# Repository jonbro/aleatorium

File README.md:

# Aleatorium

A lua scriptable buddha box board swap.

The hardware on this project is forked from [Eric Brombaugh's RP2040 boardswap for buddha boxes](https://github.com/emeb/RP2040_Projects/tree/main/buddhabox). I'm so glad he opensourced this, a programmable buddha machine is something that I've long wanted.

The firmware contains an lua scriptable 8 channel synthesizer and sequencer. The synth has the following features:
- oscilators from MI braids  
- 1 assignable lfo + 2 semi assignable Envs per voice
- lowpass filter per voice
- reverb & delay send per voice

The sequencer is a callback that is run at 96ppq. All further sequencing must be done by you.

You write new songs for aleatorium by connecting to it with usb, and loading lua scripts onto it with the [web based code editor](https://github.com/jonbro/aleatorium-editor).

## Scripting API

The scripting interface is quite simple, but there are some example files, [jam1](Firmware/jam1.lua) and [jam2](Firmware/jam2.lua). The [globals.lua file](Firmware/globals.lua) contains parameter constants for altering the synth voices.

```
-- setParam(voiceNumber, targetParameter, value)
-- voiceNumber: 0-7, the voice you want to set
-- targetParameter: use the params table from globals.lua
-- value: 0-255. Some parameters take a value from globals here, see below
setParam(0, param.timbre, 80)

-- playNote(voiceNumber, midiNoteValue)
-- voiceNumber: 0-7, the voice you want to set
-- midiNoteValue: 60 is middle c
playNote(0, 60)

-- tempoSync
-- called 96 times per quarternote. Currently there is no way to set the bpm other than recompling the firmware.

function tempoSync()

end

-- Special param targets:

-- shape - pick the voice shape, these are a subset of the oscilators from MI Braids
setParam(0, param.shape, shape.morph)

-- Env target - env1Target always goes to volume and the assigned target, env2Target only goes to the assigned target
setParam(0, param.env1Target, envTarget.cutoff)

-- LFO target - can be sent into params including env parameters
setParam(0, param.lfo1Target, lfoTarget.env12Attack)

```

## Editor notes

[A live version of the editor is available here](https://jonbro.github.io/aleatorium-editor/). Requires a non-firefox browser, due to using webserial. Make sure you connect to the device before you start trying to use it.

Use `ctrl+p` to send the current script to device and execute. You can run the following commands in the console:

```

-- save
-- provide a filename without quotes to save the file. This will add it to the set of songs that is looped through when pressing the button.
-- scripts are limited to a maximum of 16k
-- folders are not currently supported
save mysong.lua

-- load
-- provide a filename without quotes to load the file. This will replace the contents of the editor with the script.
-- folders are not currently supported. You cannot load the globals file.
load mysong.lua

-- del / rm
-- provide a filename without quotes to delete the file. This will remove it from the filesystem, and it will no longer be part of the songs on device
rm mysong.lua
```

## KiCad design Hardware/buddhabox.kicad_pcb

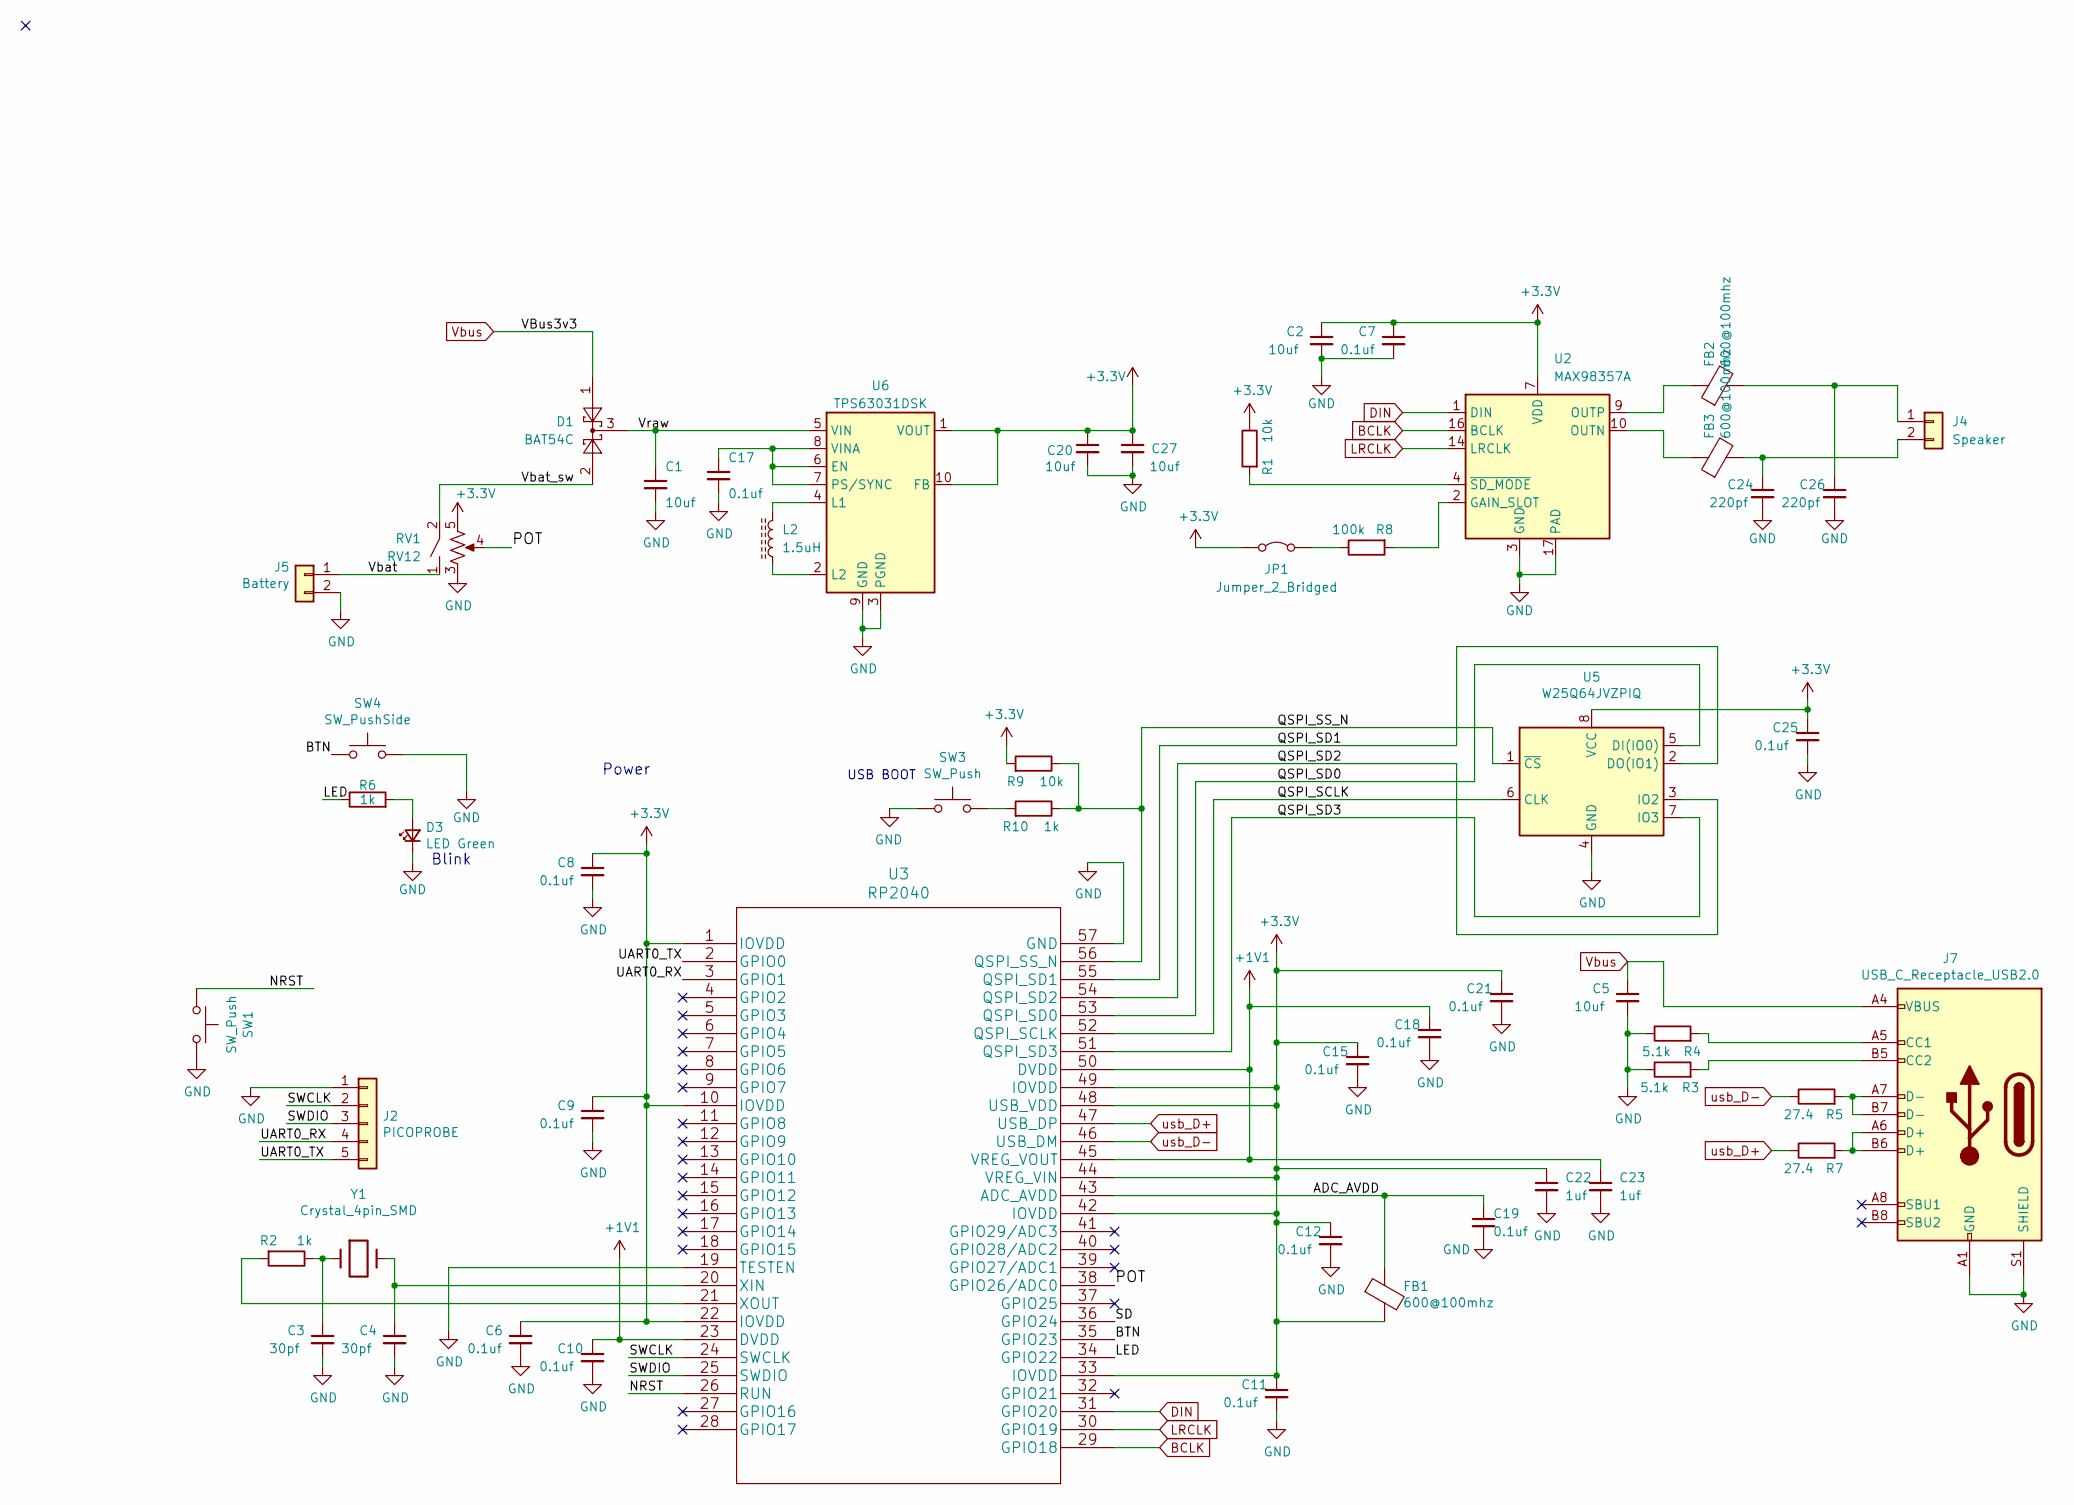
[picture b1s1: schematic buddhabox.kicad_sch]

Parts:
C1, C2, C5, C20, C27: 10uf; C_0402_1005Metric; LCSC C15525
C3, C4: 30pf; C_0603_1608Metric; LCSC C1658
C6, C7, C8, C9, C10, C11, C12, C15, C17, C18, C19, C21, C25: 0.1uf; C_0402_1005Metric; LCSC C1525
C22, C23: 1uf; C_0402_1005Metric; LCSC C52923
C24, C26: 220pf; C_0402_1005Metric; LCSC C1530
D1: BAT54C; SOT-23; LCSC C556168
D3: LED Green; LED_0603_1608Metric; LCSC C2286
FB1, FB2, FB3: 600@100mhz; L_0603_1608Metric; LCSC C1002
J2: PICOPROBE; PinHeader_1x05_P2.54mm_Vertical
J4: Speaker; PinHeader_1x02_P2.54mm_Vertical
J5: Battery; PinHeader_1x02_P2.54mm_Vertical
J7: USB_C_Receptacle_USB2.0; USB-C_SMD-TYPE-C-31-M-12; LCSC C165948
JP1: Jumper_2_Bridged; SolderJumper-2_P1.3mm_Bridged_Pad1.0x1.5mm
L2: 1.5uH; L_Coilcraft_LPS3010; LCSC C17382749
R1, R9: 10k; R_0402_1005Metric; LCSC C25744
R2, R6, R10: 1k; R_0402_1005Metric; LCSC C11702
R3, R4: 5.1k; R_0402_1005Metric; LCSC C25905
R5, R7: 27.4; R_0402_1005Metric; LCSC C31439
R8: 100k; R_0805_2012Metric; LCSC C149504
RV1: RV12
SW1, SW3: SW_Push; SW_Push_1P1T_NO_CK_KMR2; LCSC C221675
SW4: SW_PushSide; SW_Tactile_SPST_Angled_PTS645Vx83-2LFS; LCSC DNP
U2: MAX98357A; TQFN-16-1EP_3x3mm_P0.5mm_EP1.23x1.23mm; LCSC C910544
U3: RP2040; LCSC C2040
U5: W25Q64JVZPIQ; WSON-8-1EP_6x5mm_P1.27mm_EP3.4x4.3mm; LCSC C2940197
U6: TPS63031DSK; WSON-10-1EP_2.5x2.5mm_P0.5mm_EP1.2x2mm; LCSC C15516
Y1: Crystal_4pin_SMD; Crystal_SMD_3225-4Pin_3.2x2.5mm; LCSC C9002

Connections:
+1V1: C10.1, C18.1, C23.1, U3.23 (DVDD), U3.45 (VREG_VOUT), U3.50 (DVDD)
+3.3V: C2.1, C6.1, C7.1, C8.1, C9.1, C11.1, C12.1, C15.1, C20.1, C21.1, C22.1, C25.1, C27.1, FB1.2, JP1.1 (A), R1.1, R9.2, RV1.5, U2.7 (VDD), U2.8 (VDD), U3.1 (IOVDD), U3.10 (IOVDD), U3.22 (IOVDD), U3.33 (IOVDD), U3.42 (IOVDD), U3.44 (VREG_VIN), U3.48 (USB_VDD), U3.49 (IOVDD), U5.8 (VCC), U6.1 (VOUT), U6.10 (FB)
/ADC_AVDD: C19.1, FB1.1, U3.43 (ADC_AVDD)
/BTN: SW4.2, U3.35 (GPIO23)
/LED: R6.1, U3.34 (GPIO22)
/NRST: SW1.1, U3.26 (RUN)
/POT: RV1.4, U3.38 (GPIO26/ADC0)
/QSPI_SCLK: U3.52 (QSPI_SCLK), U5.6 (CLK)
/QSPI_SD0: U3.53 (QSPI_SD0), U5.5 (DI(IO0))
/QSPI_SD1: U3.55 (QSPI_SD1), U5.2 (DO(IO1))
/QSPI_SD2: U3.54 (QSPI_SD2), U5.3 (IO2)
/QSPI_SD3: U3.51 (QSPI_SD3), U5.7 (IO3)
/QSPI_SS_N: R9.1, R10.1, U3.56 (QSPI_SS_N), U5.1 (~CS)
/SD: U3.36 (GPIO24)
/SWCLK: J2.2, U3.24 (SWCLK)
/SWDIO: J2.3, U3.25 (SWDIO)
/UART0_RX: J2.4, U3.3 (GPIO1)
/UART0_TX: J2.5, U3.2 (GPIO0)
/Vbat: J5.1, RV1.1
/Vbat_sw: D1.2, RV1.2
/Vraw: C1.1, D1.3, U6.5 (VIN)
BCLK: U2.16 (BCLK), U3.29 (GPIO18)
DIN: U2.1 (DIN), U3.31 (GPIO20)
GND: C1.2, C2.2, C3.2, C4.2, C5.2, C6.2, C7.2, C8.2, C9.2, C10.2, C11.2, C12.2, C15.2, C17.2, C18.2, C19.2, C20.2, C21.2, C22.2, C23.2, C24.2, C25.2, C26.2, C27.2, D3.1 (K), J2.1, J5.2, J7.A1 (GND), J7.A12 (GND), J7.B1 (GND), J7.B12 (GND), J7.S1 (SHIELD), R3.1, R4.1, RV1.3, SW1.2, SW3.2, SW4.1, U2.3 (GND), U2.11 (GND), U2.15 (GND), U2.17 (PAD), U3.19 (TESTEN), U3.57 (GND), U5.4 (GND), U6.3 (PGND), U6.9 (GND), U6.11 (PGND)
LRCLK: U2.14 (LRCLK), U3.30 (GPIO19)
unnamed: C3.1, R2.1, Y1.1
unnamed: D3.2 (A), R6.2
unnamed: C26.1, FB2.2, J4.1
unnamed: C24.1, FB3.2, J4.2
unnamed: J7.A5 (CC1), R4.2
unnamed: J7.B5 (CC2), R3.2
unnamed: J7.A6 (D+), J7.B6 (D+), R7.2
unnamed: J7.A7 (D-), J7.B7 (D-), R5.2
unnamed: JP1.2 (B), R8.1
unnamed: R10.2, SW3.1
unnamed: R8.2, U2.2 (GAIN_SLOT)
unnamed: FB3.1, U2.10 (OUTN)
unnamed: FB2.1, U2.9 (OUTP)
unnamed: R1.2, U2.4 (~SD_MODE)
unnamed: C4.1, U3.20 (XIN), Y1.3
unnamed: R2.2, U3.21 (XOUT)
unnamed: C17.1, U6.6 (EN), U6.7 (PS/SYNC), U6.8 (VINA)
unnamed: L2.2, U6.4 (L1)
unnamed: L2.1, U6.2 (L2)
Vbus: C5.1, D1.1, J7.A4 (VBUS), J7.A9 (VBUS), J7.B4 (VBUS), J7.B9 (VBUS)
usb_D+: R7.1, U3.47 (USB_DP)
usb_D-: R5.1, U3.46 (USB_DM)

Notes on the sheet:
USB BOOT
Blink
Power

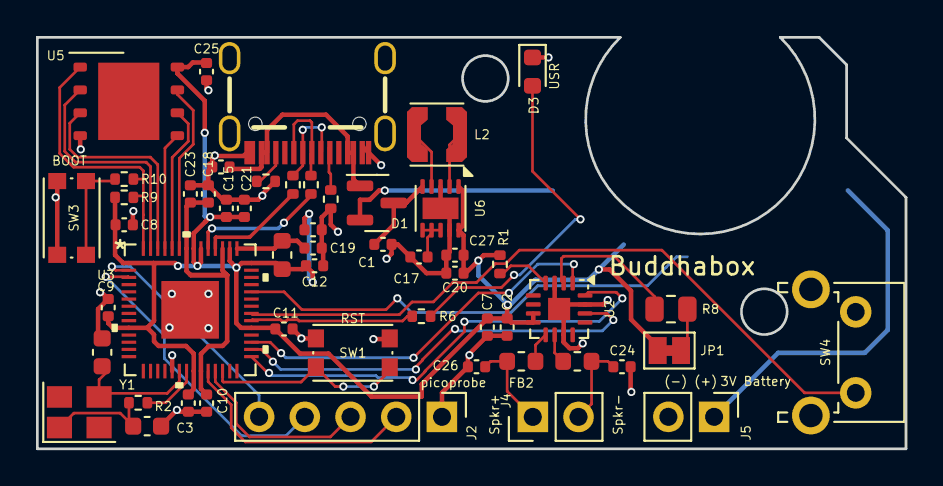
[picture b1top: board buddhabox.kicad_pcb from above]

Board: 2 copper layers, 48.3 x 22.9 mm, 54 parts (1 on the bottom side), 46 nets.

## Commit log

2024-06-07 quick readme & license fixup
2024-06-07 correctly license
2024-06-07 Added some notes on using the editor
2024-06-08 cleanup and clarify final mix stage
2024-06-08 minorly correct documentation
2024-06-10 move example files around, add startup delay
2024-06-10 tlv320aic3204 driver version
2024-06-16 cross hardware support
2024-06-16 global volume starts at zero so we don't get a pop at the beginning while the ADC settles.
2024-06-21 potentiometer, new jam
2024-06-21 Correct for crossplatform build

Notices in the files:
Hardware/buddhabox.kicad_pcb:
(c) 2022 E. Brombaugh
(c) 2024 J. Brodsky
parts and their libraries:
Copyright 2021 Accelerated Designs. All rights reserved.
